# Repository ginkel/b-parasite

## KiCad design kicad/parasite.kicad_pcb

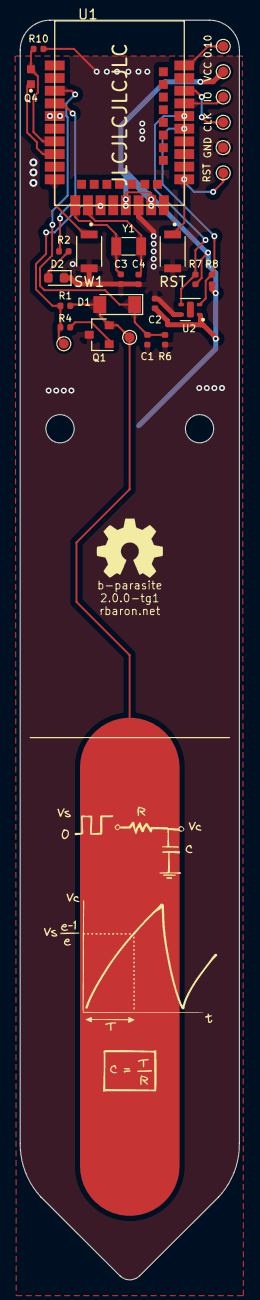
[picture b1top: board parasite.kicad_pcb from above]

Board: 2 copper layers, 22.0 x 126.4 mm, 29 parts (1 on the bottom side), 19 nets.

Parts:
BT1: Battery_Cell; BatteryHolder_Keystone_3002_1x2032
C1: 1n; C_0402_1005Metric
C2: 100n; C_0402_1005Metric
C3, C4: 12p; C_0402_1005Metric
D1: LL4148; D_MiniMELF
D2: LED; LED_0603_1608Metric
Q1: MMBT3906; SOT-23
Q4: Q_Photo_NPN; TR8
R1, R4, R7, R8: 10k; R_0402_1005Metric
R2: 1k; R_0402_1005Metric
R6: 1M; R_0402_1005Metric
R10: 470; R_0402_1005Metric
RST1: B3U-1000P; SW_B3U-1000P
SW1: B3U-1000P; SW_B3U-1000P
TP1: IO; TestPoint_Pad_D1.0mm
TP2: CLK; TestPoint_Pad_D1.0mm
TP3: GND; TestPoint_Pad_D1.0mm
TP4: RST; TestPoint_Pad_D1.0mm
TP5: CPARA; TestPoint_Pad_D1.0mm
TP6: PWM; TestPoint_Pad_D1.0mm
TP7: VCC; TestPoint_Pad_D1.0mm
TP8: 0.10; TestPoint_Pad_D1.0mm
U1: E73-2G4M08S1C
U2: SHTC3; Sensirion_DFN-4-1EP_2x2mm_P1mm_EP0.7x1.6mm
Y1: 32.768kHz; Crystal_SMD_3215-2Pin_3.2x1.5mm

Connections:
0.10: TP8.1, U1.43 (P0.10/NFC2)
+3V0: BT1.1 (+), C2.1, R7.2, R8.1, TP7.1, U1.19 (VDD), U1.23 (VDDH), U2.1 (VDD)
BTN1: SW1.1, U1.10 (P0.30/AIN6)
CPARA: D1.2 (A), Q1.2 (E), R1.2, TP5.1
GND: BT1.2 (-), C1.2, C2.2, C3.1, C4.2, D2.1 (K), Q1.3 (C), R6.2, R10.1, RST1.2, SW1.2, TP3.1, U1.5 (GND@1), U1.21 (GND@2), U2.4 (VSS)
LED: R2.2, U1.4 (P0.28/AIN4)
unnamed: D2.2 (A), R2.1
unnamed: Q1.1 (B), R4.1
unnamed: C3.2, U1.11 (P0.00/XL1), Y1.2
unnamed: C4.1, U1.13 (P0.01/XL2), Y1.1
PHOTO_OUT: Q4.2 (E), R10.2, U1.7 (P0.02/AIN0)
PHOTO_V: Q4.1 (C), U1.8 (P0.29/AIN5)
PWM: R1.1, R4.2, TP6.1, U1.15 (P0.05/AIN3)
RST: RST1.1, TP4.1, U1.26 (P0.18/RESET)
SCL: R8.2, U1.33 (P0.13), U2.2 (SCL)
SDA: R7.1, U1.35 (P0.24), U2.3 (SDA)
SENS_OUT: C1.1, D1.1 (K), R6.1, U1.3 (P0.03/AIN1)
SWDCLK: TP2.1, U1.39 (SWDCLK)
SWDIO: TP1.1, U1.37 (SWDIO)

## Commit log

2023-05-12 Rounded PCB edges
